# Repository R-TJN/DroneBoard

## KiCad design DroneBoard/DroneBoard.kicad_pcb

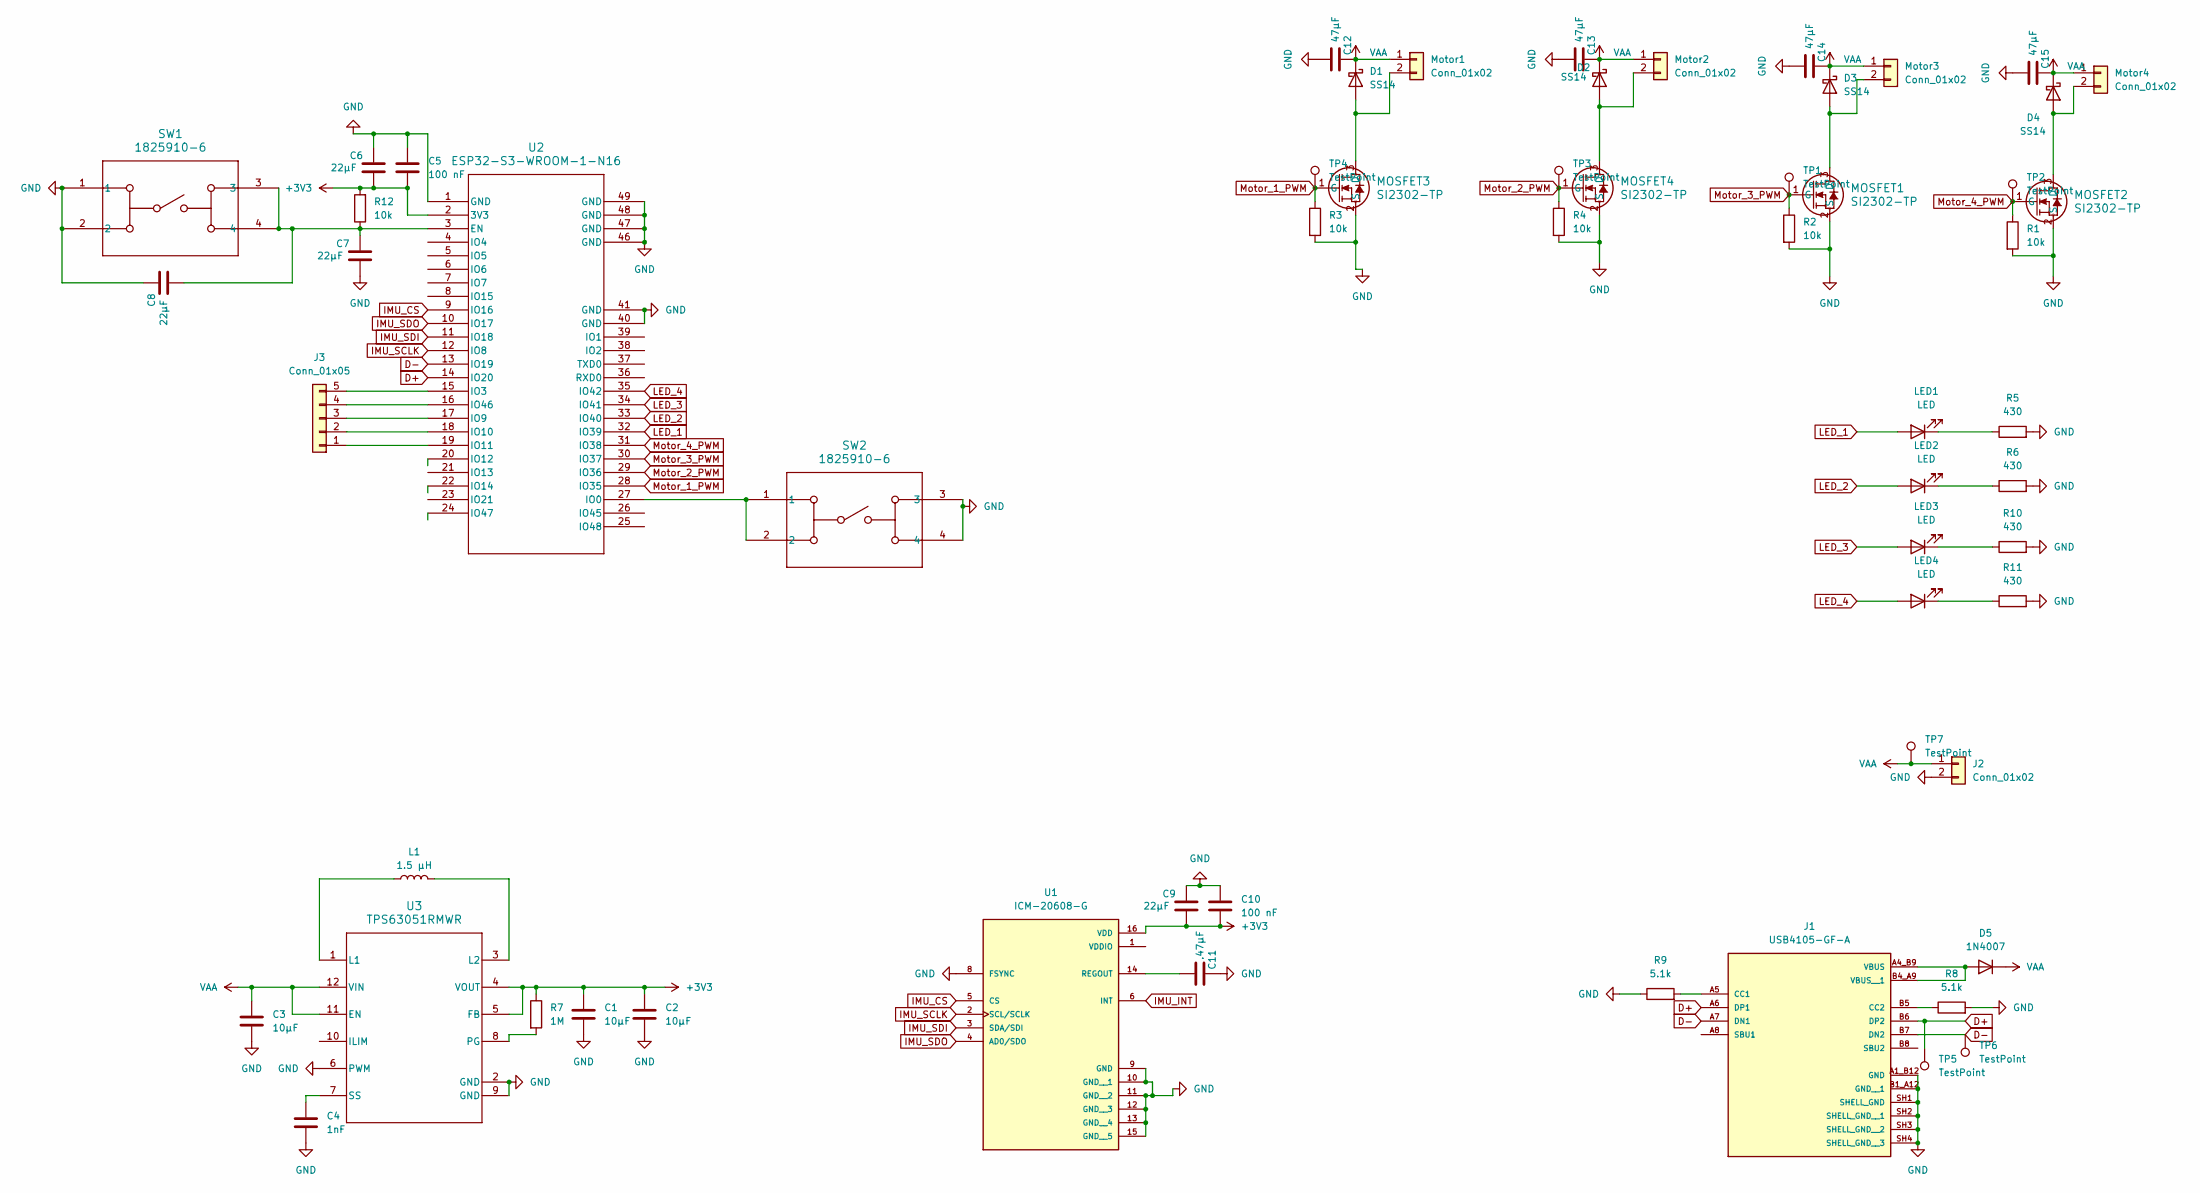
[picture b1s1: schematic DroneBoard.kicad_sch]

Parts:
C1, C2, C3: 10μF; C_0603_1608Metric_Pad1.08x0.95mm_HandSolder
C4: 1nF; C_0603_1608Metric_Pad1.08x0.95mm_HandSolder
C5, C10: 100 nF; C_0603_1608Metric_Pad1.08x0.95mm_HandSolder
C6, C7, C8, C9: 22μF; C_0603_1608Metric_Pad1.08x0.95mm_HandSolder
C11: .47μF; C_0603_1608Metric_Pad1.08x0.95mm_HandSolder
C12, C13, C14, C15: 47μF; C_0603_1608Metric_Pad1.08x0.95mm_HandSolder
D1, D2, D3, D4: SS14; D_SMA
D5: 1N4007; D_SMA
J1: USB4105-GF-A; GCT_USB4105-GF-A; PARTREV B4
J2: Conn_01x02; JST_PH_B2B-PH-K_1x02_P2.00mm_Vertical
J3: Conn_01x05; PinSocket_1x05_P2.54mm_Vertical
L1: 1.5 μH; C_0603_1608Metric_Pad1.08x0.95mm_HandSolder
LED1, LED2, LED3, LED4: LED; LED_0603_1608Metric_Pad1.05x0.95mm_HandSolder
MOSFET1, MOSFET2, MOSFET3, MOSFET4: SI2302-TP; SOT-23_MCC
Motor1, Motor2, Motor3, Motor4: Conn_01x02; JST_EH_B2B-EH-A_1x02_P2.50mm_Vertical
R1, R2, R3, R4, R12: 10k; R_0603_1608Metric_Pad0.98x0.95mm_HandSolder
R5, R6, R10, R11: 430; R_0603_1608Metric_Pad0.98x0.95mm_HandSolder
R7: 1M; R_0603_1608Metric_Pad0.98x0.95mm_HandSolder
R8, R9: 5.1k; R_0603_1608Metric_Pad0.98x0.95mm_HandSolder
SW1, SW2: 1825910-6; SW4_1825910-B_TEC
TP1, TP2, TP3, TP4, TP5, TP6, TP7: TestPoint; Pin_D1.0mm_L10.0mm
U1: ICM-20608-G; PQFN50P300X300X80-16N; PARTREV 1.0
U2: ESP32-S3-WROOM-1-N16; ESP32-S3-WROOM-1_EXP
U3: TPS63051RMWR; RMW0012A

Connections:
+3V3: C1.1, C2.1, C5.2, C6.2, C9.2, C10.2, R7.1, R12.2, U1.16 (VDD), U2.2 (3V3), U3.4 (VOUT), U3.5 (FB)
D+: J1.A6 (DP1), J1.B6 (DP2), TP5.1, U2.14 (IO20)
D-: J1.A7 (DN1), J1.B7 (DN2), TP6.1, U2.13 (IO19)
GND: C1.2, C2.2, C3.2, C4.2, C5.1, C6.1, C7.2, C8.1, C9.1, C10.1, C11.1, C12.2, C13.2, C14.2, C15.2, J1.A1_B12 (GND), J1.B1_A12 (GND__1), J1.SH1 (SHELL_GND), J1.SH2 (SHELL_GND__1), J1.SH3 (SHELL_GND__2), J1.SH4 (SHELL_GND__3), J2.2, MOSFET1.2 (S), MOSFET2.2 (S), MOSFET3.2 (S), MOSFET4.2 (S), R1.2, R2.2, R3.2, R4.2, R5.2, R6.2, R8.2, R9.1, R10.2, R11.2, SW1.1, SW1.2, SW2.3, SW2.4, U1.8 (FSYNC), U1.9 (GND), U1.10 (GND__1), U1.11 (GND__2), U1.12 (GND__3), U1.13 (GND__4), U1.15 (GND__5), U2.1 (GND), U2.40 (GND), U2.41 (GND), U2.46 (GND), U2.47 (GND), U2.48 (GND), U2.49 (GND), U3.2 (GND), U3.6 (PWM), U3.9 (GND)
IMU_CS: U1.5 (CS), U2.9 (IO16)
IMU_INT: U1.6 (INT)
IMU_SCLK: U1.2 (SCL/SCLK), U2.12 (IO8)
IMU_SDI: U1.3 (SDA/SDI), U2.11 (IO18)
IMU_SDO: U1.4 (AD0/SDO), U2.10 (IO17)
LED_1: LED1.2 (A), U2.32 (IO39)
LED_2: LED2.2 (A), U2.33 (IO40)
LED_3: LED3.2 (A), U2.34 (IO41)
LED_4: LED4.2 (A), U2.35 (IO42)
Motor_1_PWM: MOSFET3.1 (G), R3.1, TP4.1, U2.28 (IO35)
Motor_2_PWM: MOSFET4.1 (G), R4.1, TP3.1, U2.29 (IO36)
Motor_3_PWM: MOSFET1.1 (G), R2.1, TP1.1, U2.30 (IO37)
Motor_4_PWM: MOSFET2.1 (G), R1.1, TP2.1, U2.31 (IO38)
unnamed: D1.2 (A), MOSFET3.3 (D), Motor1.2
unnamed: D2.2 (A), MOSFET4.3 (D), Motor2.2
unnamed: D3.2 (A), MOSFET1.3 (D), Motor3.2
unnamed: D4.2 (A), MOSFET2.3 (D), Motor4.2
unnamed: D5.2 (A), J1.A4_B9 (VBUS), J1.B4_A9 (VBUS__1)
unnamed: J1.A5 (CC1), R9.2
unnamed: J1.B5 (CC2), R8.1
unnamed: J3.1, U2.19 (IO11)
unnamed: J3.2, U2.18 (IO10)
unnamed: J3.3, U2.17 (IO9)
unnamed: J3.4, U2.16 (IO46)
unnamed: J3.5, U2.15 (IO3)
unnamed: LED1.1 (K), R5.1
unnamed: LED2.1 (K), R6.1
unnamed: LED3.1 (K), R10.1
unnamed: LED4.1 (K), R11.1
unnamed: C11.2, U1.14 (REGOUT)
unnamed: C7.1, C8.2, R12.1, SW1.3, SW1.4, U2.3 (EN)
unnamed: SW2.1, SW2.2, U2.27 (IO0)
unnamed: L1.1, U3.1 (L1)
unnamed: L1.2, U3.3 (L2)
unnamed: R7.2, U3.8 (PG)
unnamed: C4.1, U3.7 (SS)
VAA: C3.1, C12.1, C13.1, C14.1, C15.1, D1.1 (K), D2.1 (K), D3.1 (K), D4.1 (K), D5.1 (K), J2.1, Motor1.1, Motor2.1, Motor3.1, Motor4.1, TP7.1, U3.11 (EN), U3.12 (VIN)

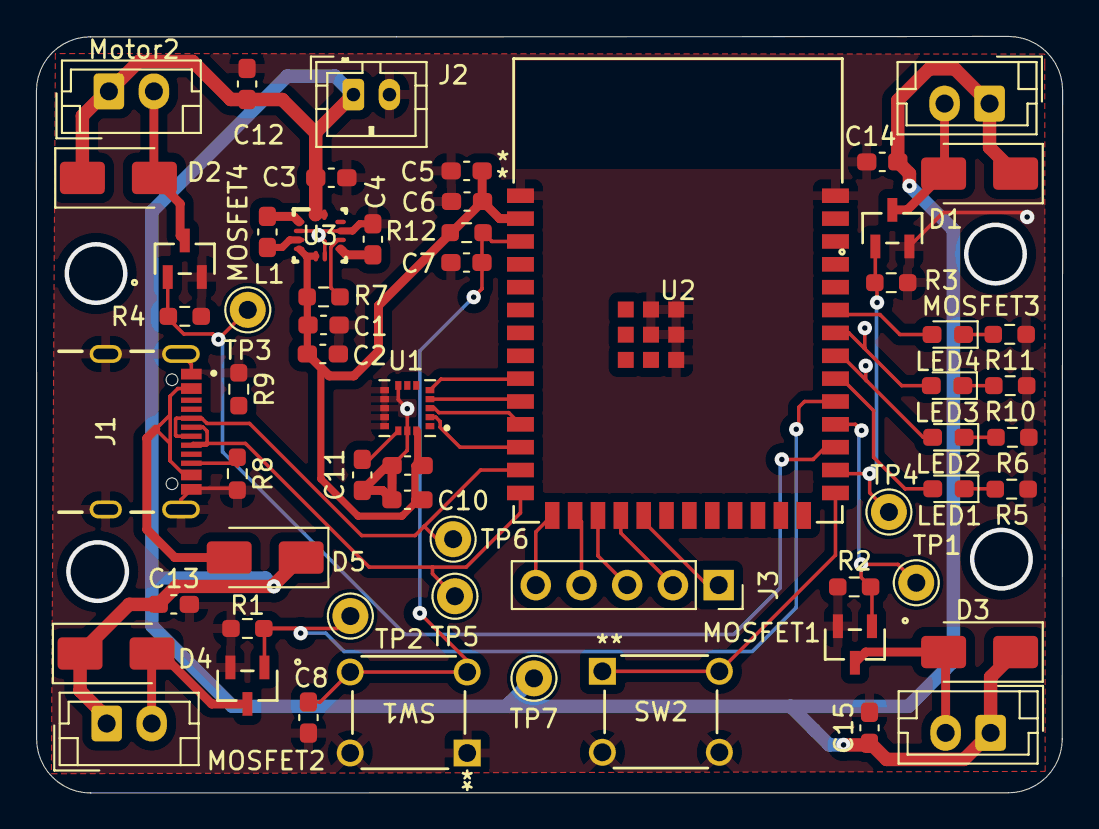
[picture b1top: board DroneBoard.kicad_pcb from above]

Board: 2 copper layers, 57.0 x 42.0 mm, 60 parts (0 on the bottom side), 40 nets.

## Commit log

2025-04-07 BOARD
2025-04-07 Fixed Schematics
    Fixed the flyback diodes
    Fixed the LED resistors and extra diodes
    Fixed the 0603 sizings
2025-04-08 Routing and some small schematic updates
2025-04-09 Mostly Routing and Power over USBC
2025-04-10 Honestly idk whats in this commit
